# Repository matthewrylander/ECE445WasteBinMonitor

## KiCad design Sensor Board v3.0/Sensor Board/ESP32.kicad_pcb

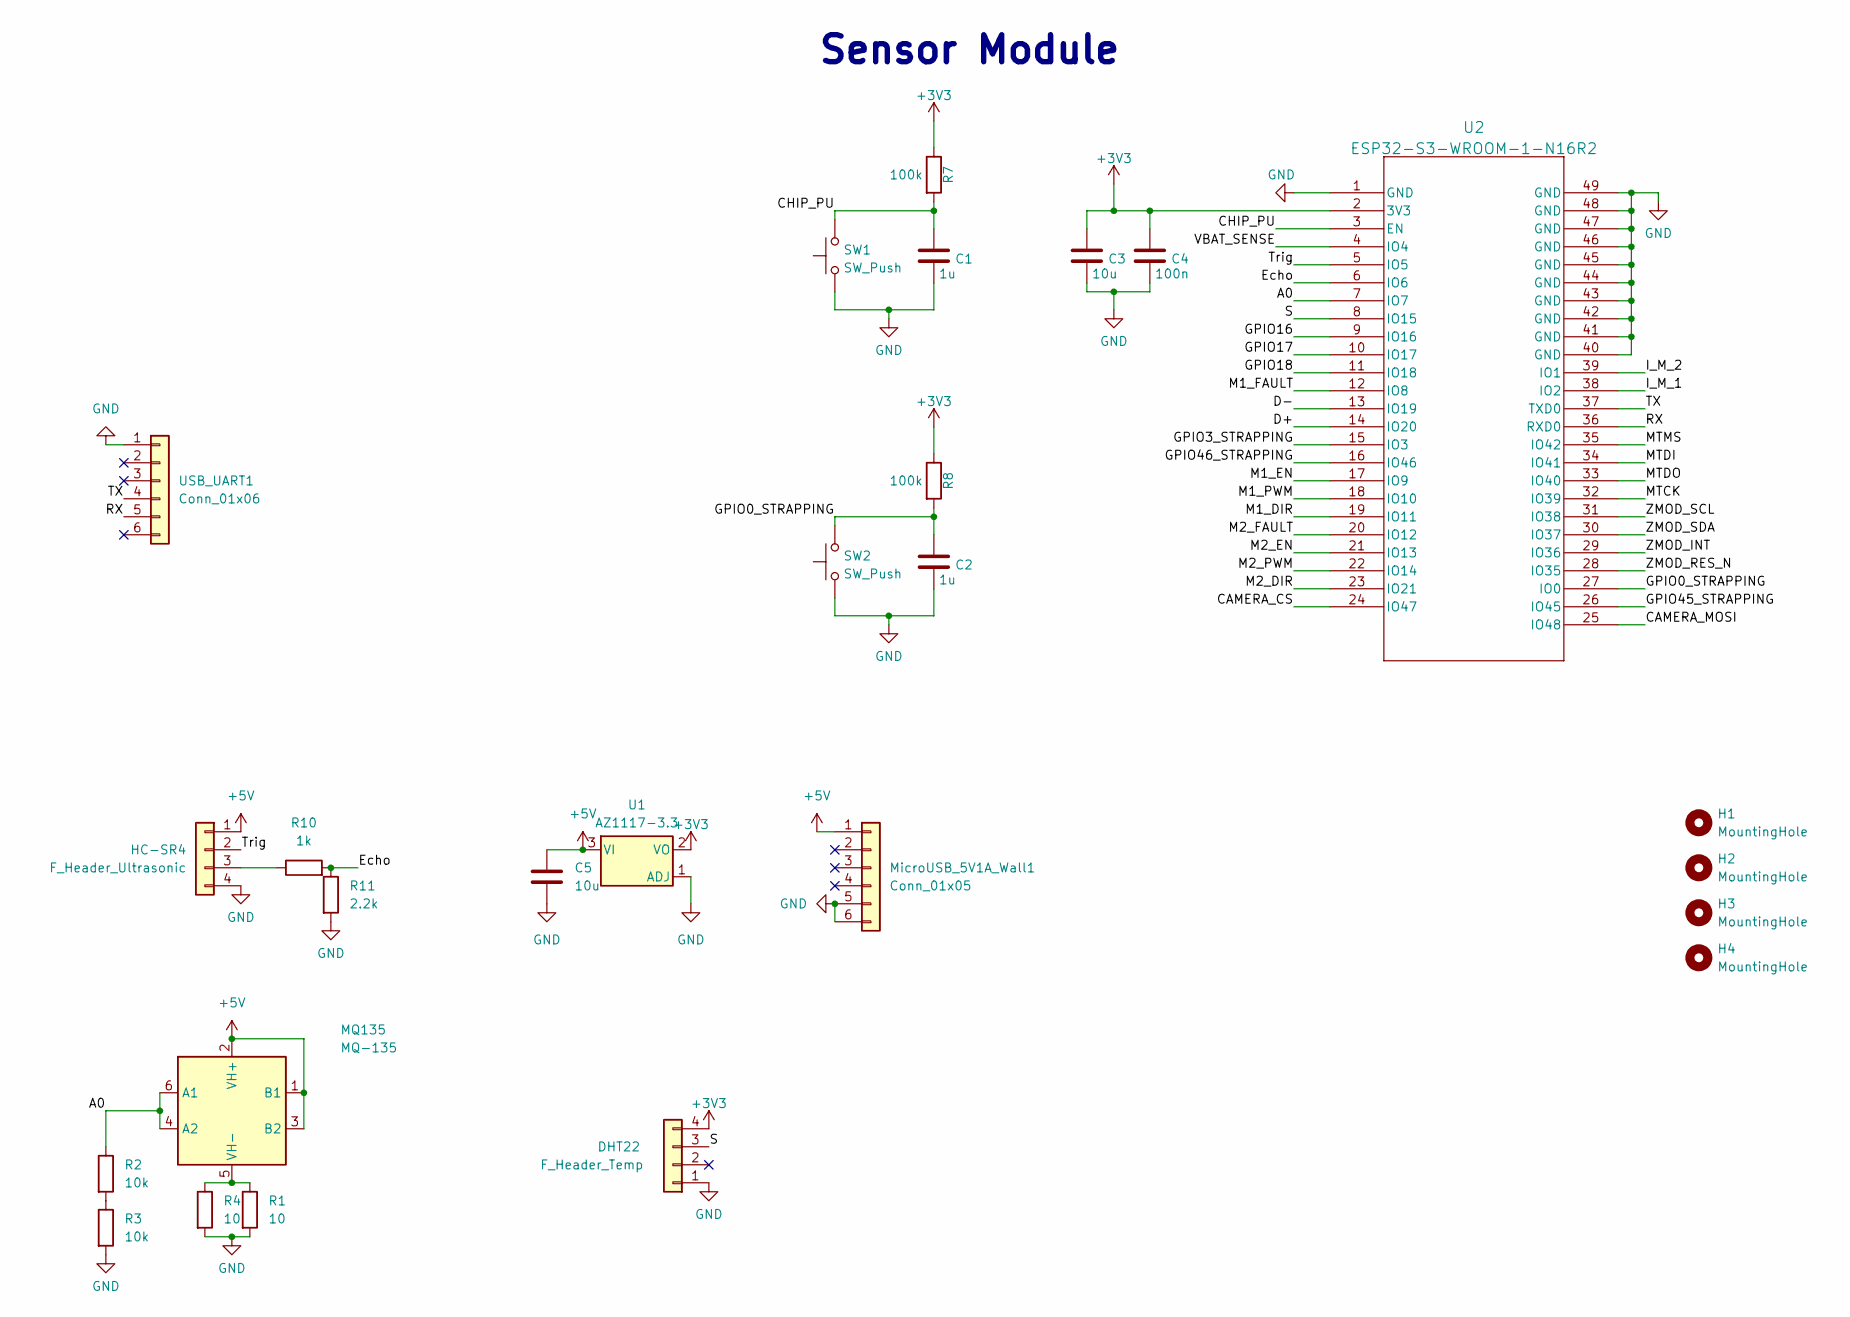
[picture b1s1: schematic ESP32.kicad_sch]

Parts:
C1, C2: 1u; C_0805_2012Metric
C3, C5: 10u; C_0805_2012Metric
C4: 100n; C_0805_2012Metric
DHT22: F_Header_Temp; PinHeader_1x04_P2.54mm_Vertical
H1, H2, H3, H4: MountingHole; MountingHole_3.2mm_M3
HC-SR4: F_Header_Ultrasonic; PinHeader_1x04_P2.54mm_Vertical
MQ135: MQ-135; MQ-6
MicroUSB_5V1A_Wall1: Conn_01x05; USB_Micro-B_Amphenol_10104110_Horizontal
R1, R4: 10; R_Axial_DIN0204_L3.6mm_D1.6mm_P5.08mm_Horizontal
R2, R3: 10k; R_0805_2012Metric
R7, R8: 100k; R_0805_2012Metric
R10: 1k; R_0805_2012Metric
R11: 2.2k; R_0805_2012Metric
SW1, SW2: SW_Push; SW_PUSH_6mm
U1: AZ1117-3.3; AZ1117C-TO252-2
U2: ESP32-S3-WROOM-1-N16R2; ESP32-S3-WROOM-1_EXP
USB_UART1: Conn_01x06; PinHeader_1x06_P2.54mm_Vertical

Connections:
+3V3: C3.1, C4.1, DHT22.4, R7.1, R8.1, U1.2 (VO), U2.2 (3V3)
+5V: C5.1, HC-SR4.1, MQ135.1 (B1), MQ135.2 (VH+), MQ135.3 (B2), MicroUSB_5V1A_Wall1.1, U1.3 (VI)
/A0: MQ135.4 (A2), MQ135.6 (A1), R2.1, U2.7 (IO7)
/CAMERA_CS: U2.24 (IO47)
/CAMERA_MOSI: U2.25 (IO48)
/CHIP_PU: C1.1, R7.2, SW1.2, U2.3 (EN)
/D+: U2.14 (IO20)
/D-: U2.13 (IO19)
/Echo: R10.2, R11.1, U2.6 (IO6)
/GPIO0_STRAPPING: C2.1, R8.2, SW2.2, U2.27 (IO0)
/GPIO3_STRAPPING: U2.15 (IO3)
/GPIO16: U2.9 (IO16)
/GPIO17: U2.10 (IO17)
/GPIO18: U2.11 (IO18)
/GPIO45_STRAPPING: U2.26 (IO45)
/GPIO46_STRAPPING: U2.16 (IO46)
/I_M_1: U2.38 (IO2)
/I_M_2: U2.39 (IO1)
/M1_DIR: U2.19 (IO11)
/M1_EN: U2.17 (IO9)
/M1_FAULT: U2.12 (IO8)
/M1_PWM: U2.18 (IO10)
/M2_DIR: U2.23 (IO21)
/M2_EN: U2.21 (IO13)
/M2_FAULT: U2.20 (IO12)
/M2_PWM: U2.22 (IO14)
/MTCK: U2.32 (IO39)
/MTDI: U2.34 (IO41)
/MTDO: U2.33 (IO40)
/MTMS: U2.35 (IO42)
/RX: U2.36 (RXD0), USB_UART1.5
/S: DHT22.3, U2.8 (IO15)
/TX: U2.37 (TXD0), USB_UART1.4
/Trig: HC-SR4.2, U2.5 (IO5)
/VBAT_SENSE: U2.4 (IO4)
/ZMOD_INT: U2.29 (IO36)
/ZMOD_RES_N: U2.28 (IO35)
/ZMOD_SCL: U2.31 (IO38)
/ZMOD_SDA: U2.30 (IO37)
GND: C1.2, C2.2, C3.2, C4.2, C5.2, DHT22.1, HC-SR4.4, MicroUSB_5V1A_Wall1.5, MicroUSB_5V1A_Wall1.6, R1.2, R3.2, R4.2, R11.2, SW1.1, SW2.1, U1.1 (ADJ), U2.1 (GND), U2.40 (GND), U2.41 (GND), U2.42 (GND), U2.43 (GND), U2.44 (GND), U2.45 (GND), U2.46 (GND), U2.47 (GND), U2.48 (GND), U2.49 (GND), USB_UART1.1
unnamed: HC-SR4.3, R10.1
unnamed: MQ135.5 (VH-), R1.1, R4.1
unnamed: R2.2, R3.1

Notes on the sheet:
Sensor Module

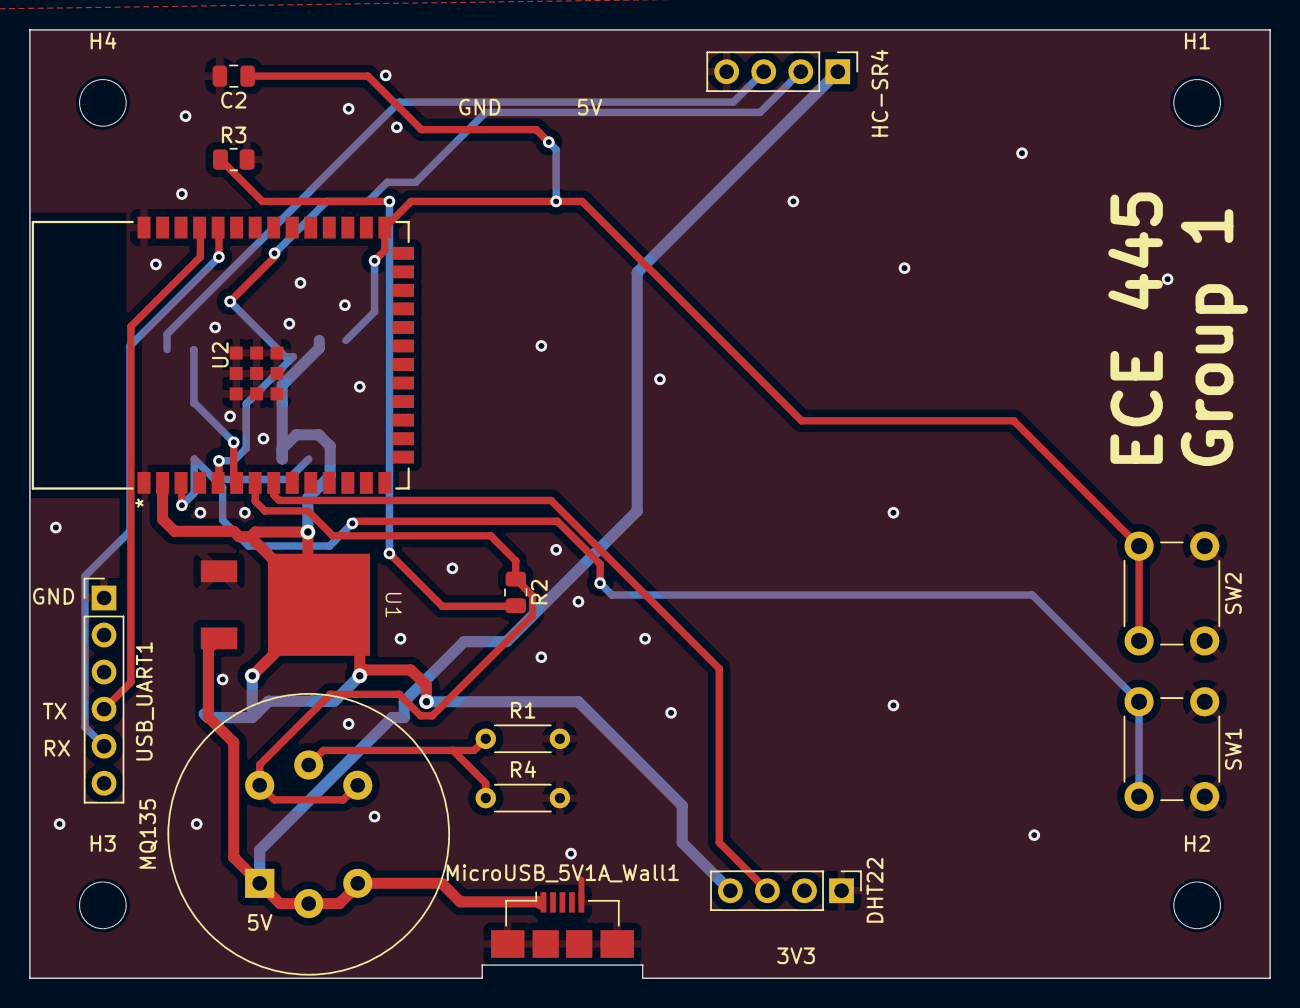
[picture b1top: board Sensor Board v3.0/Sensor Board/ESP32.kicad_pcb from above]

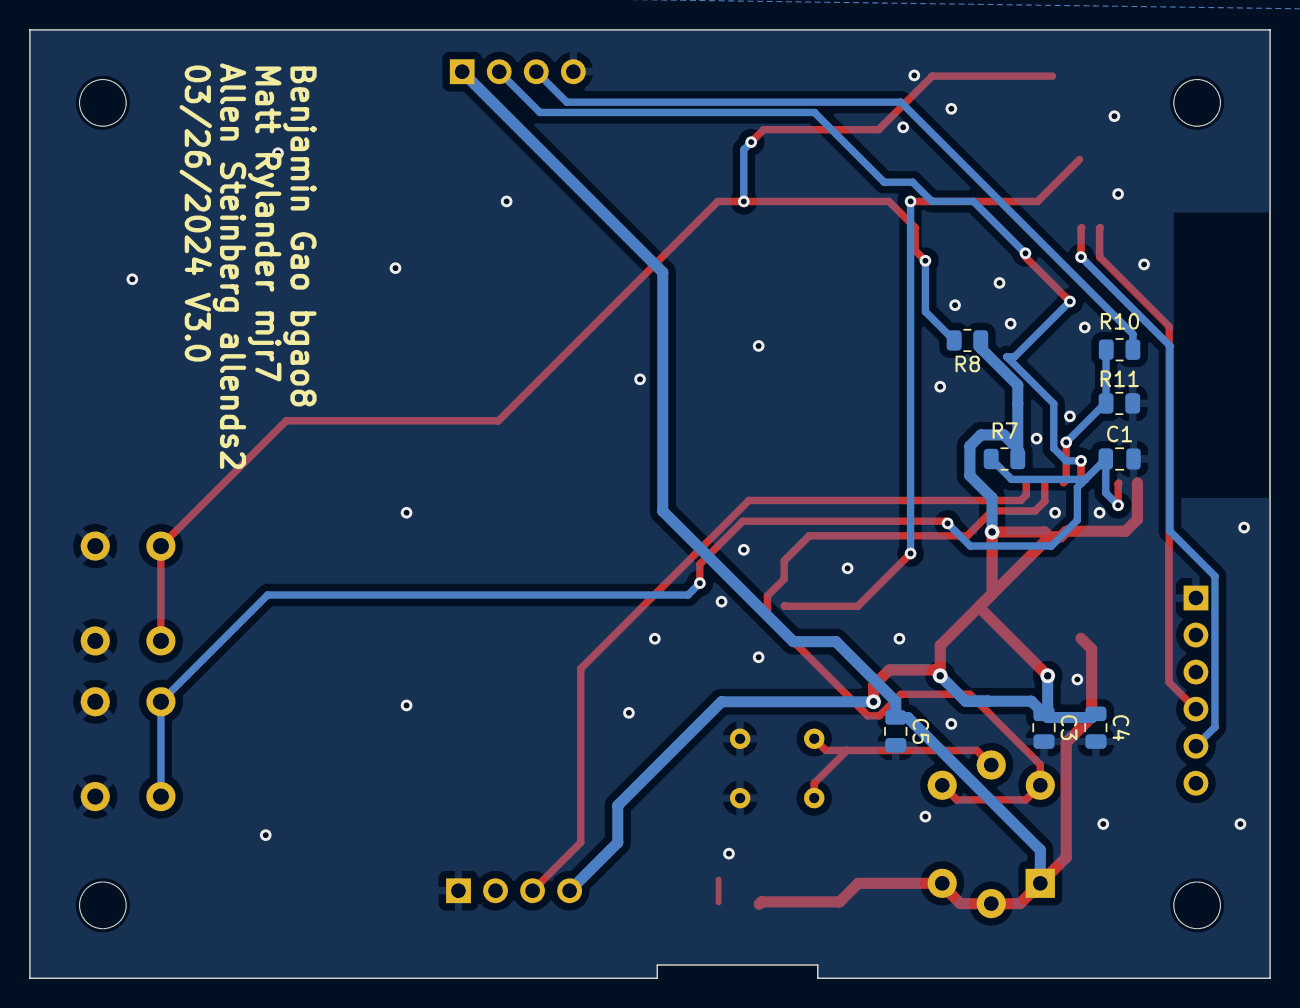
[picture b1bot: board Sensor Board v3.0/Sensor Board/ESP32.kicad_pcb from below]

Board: 2 copper layers, 85.0 x 65.0 mm, 26 parts (8 on the bottom side), 14 nets.

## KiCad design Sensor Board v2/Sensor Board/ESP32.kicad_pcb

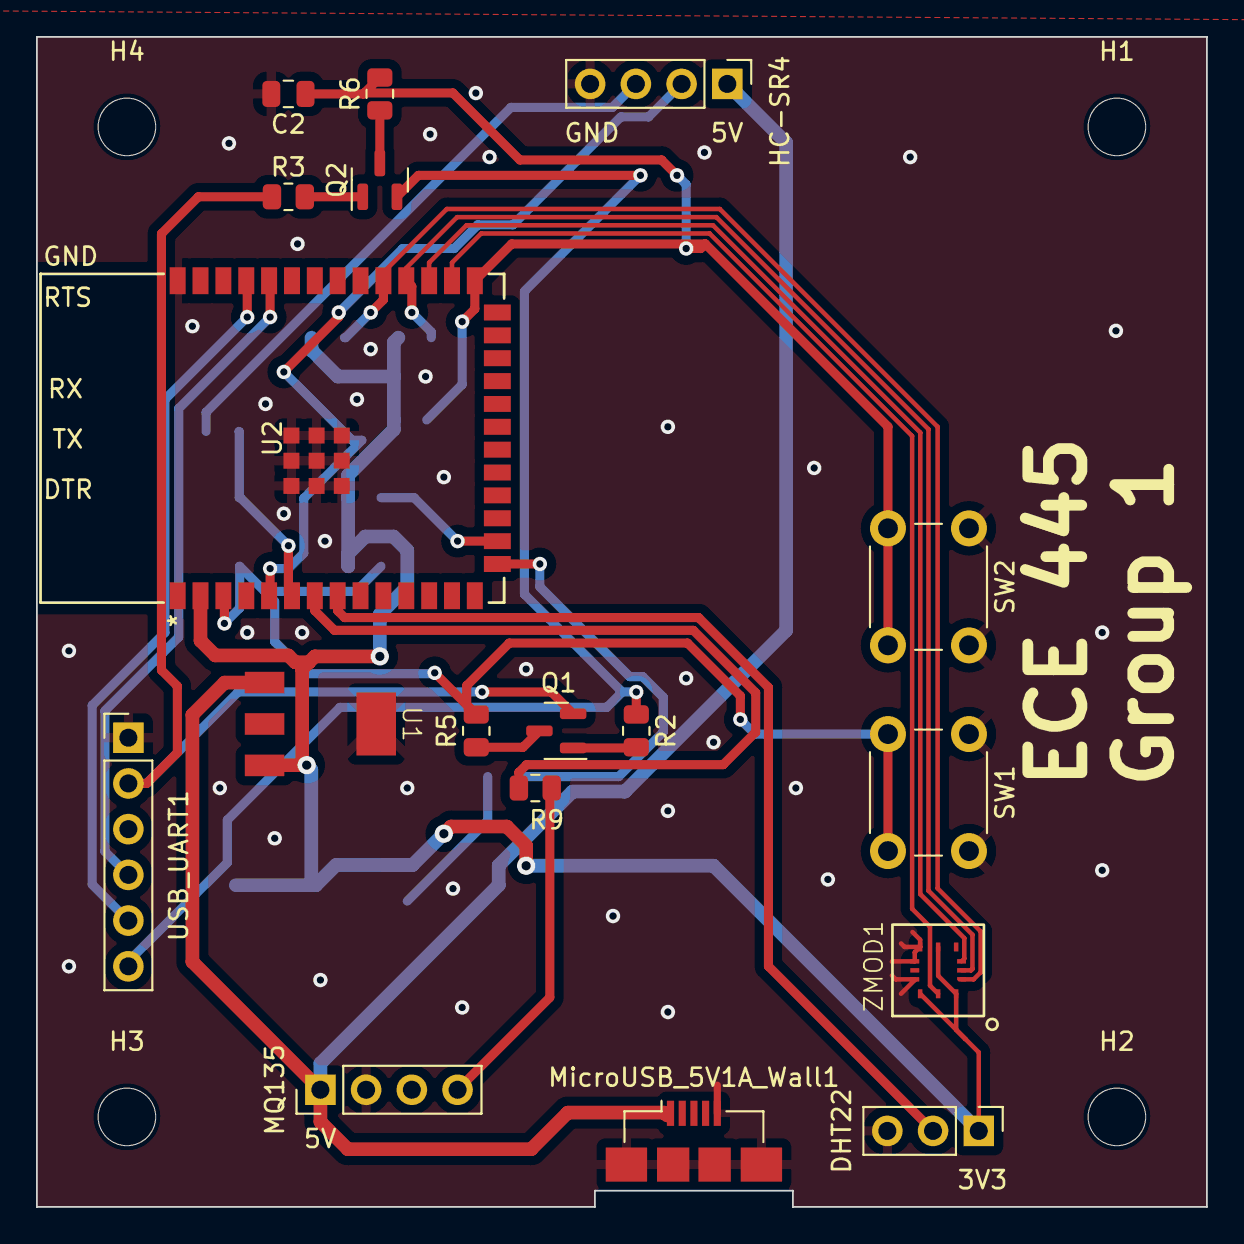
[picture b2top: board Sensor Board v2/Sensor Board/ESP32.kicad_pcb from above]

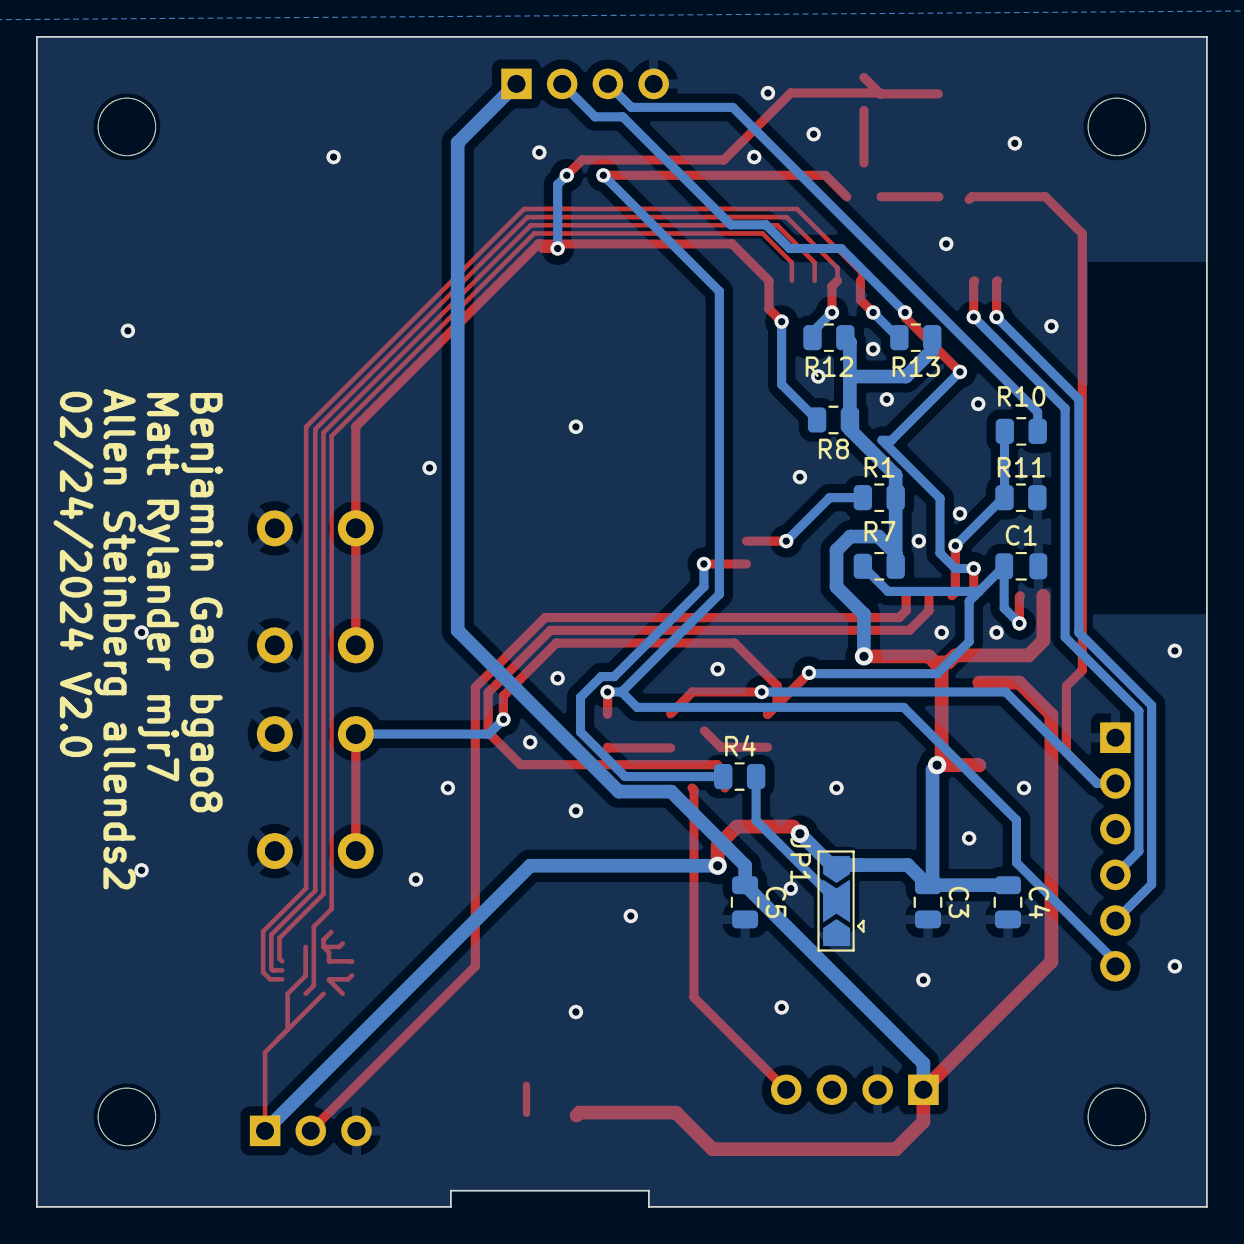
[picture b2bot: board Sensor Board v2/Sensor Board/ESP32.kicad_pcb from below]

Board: 2 copper layers, 65.0 x 65.0 mm, 35 parts (13 on the bottom side), 26 nets.

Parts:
C1, C2: 1u; C_0805_2012Metric
C3, C5: 10u; C_0805_2012Metric
C4: 100n; C_0805_2012Metric
DHT22: F_Header_Temp; PinHeader_1x03_P2.54mm_Vertical
H1, H2, H3, H4: MountingHole; MountingHole_3.2mm_M3
HC-SR4: F_Header_Ultrasonic; PinHeader_1x04_P2.54mm_Vertical
JP1: SolderJumper_3_Open; SolderJumper-3_P2.0mm_Open_TrianglePad1.0x1.5mm
MQ135: Gas Sensor; PinHeader_1x04_P2.54mm_Vertical
MicroUSB_5V1A_Wall1: Conn_01x05; USB_Micro-B_Amphenol_10104110_Horizontal
Q1, Q2: SS8050-G; SOT-23
R1, R4, R9, R10: 1k; R_0805_2012Metric
R2, R3, R5, R6, R12, R13: 10k; R_0805_2012Metric
R7, R8: 100k; R_0805_2012Metric
R11: 2.2k; R_0805_2012Metric
SW1, SW2: SW_Push; SW_PUSH_6mm
U1: AZ1117-3.3; AZ1117C-SOT223
U2: ESP32-S3-WROOM-1-N16R2; ESP32-S3-WROOM-1_EXP
USB_UART1: Conn_01x06; PinHeader_1x06_P2.54mm_Vertical
ZMOD1: ZMOD4410

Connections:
+3V3: C3.1, C4.1, DHT22.1, JP1.3 (B), R1.2, R7.1, R8.1, R12.1, R13.1, U1.3 (VO), U2.2 (3V3), ZMOD1.5 (VDD), ZMOD1.10 (VDDH), ZMOD1.12 (VDDIO)
+5V: C5.1, HC-SR4.1, MQ135.1, MicroUSB_5V1A_Wall1.1, U1.1 (VI)
/A0: R9.1, U2.7 (IO7)
/CHIP_PU: C1.1, R5.2, R7.2, SW1.2, U2.3 (EN)
/DTR: Q2.2 (E), R2.1, USB_UART1.6
/Echo: R10.2, R11.1, U2.6 (IO6)
/GPIO0_STRAPPING: C2.1, R6.2, R8.2, SW2.2, U2.27 (IO0)
/GPIO3_STRAPPING: R4.1, U2.15 (IO3)
/GPIO46_STRAPPING: R1.1, U2.16 (IO46)
/RTS: Q1.2 (E), R3.1, USB_UART1.2
/RX: U2.36 (RXD0), USB_UART1.4
/S: DHT22.2, U2.8 (IO15)
/TX: U2.37 (TXD0), USB_UART1.5
/Trig: HC-SR4.2, U2.5 (IO5)
/ZMOD_INT: U2.29 (IO36), ZMOD1.3 (INT)
/ZMOD_RES_N: U2.28 (IO35), ZMOD1.11 (RES_N)
/ZMOD_SCL: R13.2, U2.31 (IO38), ZMOD1.1 (SCL)
/ZMOD_SDA: R12.2, U2.30 (IO37), ZMOD1.2 (SDA)
GND: C1.2, C2.2, C3.2, C4.2, C5.2, DHT22.3, HC-SR4.4, JP1.1 (A), MQ135.2, MicroUSB_5V1A_Wall1.5, MicroUSB_5V1A_Wall1.6, R11.2, SW1.1, SW2.1, U1.4 (ADJ), U2.1 (GND), U2.40 (GND), U2.41 (GND), U2.42 (GND), U2.43 (GND), U2.44 (GND), U2.45 (GND), U2.46 (GND), U2.47 (GND), U2.48 (GND), U2.49 (GND), USB_UART1.1, ZMOD1.6 (VSS), ZMOD1.7 (VSS), ZMOD1.9 (VSS)
unnamed: HC-SR4.3, R10.1
unnamed: JP1.2 (C), R4.2
unnamed: MQ135.4, R9.2
unnamed: Q1.1 (B), R2.2
unnamed: Q1.3 (C), R5.1
unnamed: Q2.1 (B), R3.2
unnamed: Q2.3 (C), R6.1

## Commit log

2024-01-29 Adding folders for notebooks and photos
2024-02-20 Update Notebook
2024-02-20 Create folder for esp files
2024-02-20 Upload schematic
    Schematic without levelshifter and needing changes
2024-02-20 Update Schematic
2024-02-20 Schematic Updates
2024-02-20 Added voltage regulators to both schematics
2024-02-21 Added PCB for sensor board
    Does not include screw holes. Ignored 4 warnings (silkscreen off board, silkscreen overlap in esp32 which was part of orig footprint, and 2 instances of the solder mask being insufficient on solder b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
2024-02-29 Add hub board v1.0 and Sensor Board v2.0
2024-02-29 Added I2C resistors
2024-03-01 Notebook
2024-03-20 Added Updated Code
2024-03-22 Updated lots of code
2024-03-23 Updated Pinout for initiator
2024-03-26 Uploaded version 2 of sensor board schematic, still needs PCB layout
2024-03-26 Add final sensor board
2024-03-26 Having fun with Nextion display
2024-04-11 updates to code/GUI
2024-04-29 Notebook test
2024-04-29 Notebook pictures
2024-04-29 webp test
2024-05-02 updated code
2024-05-02 updated notebook
2024-05-02 Cleaned up files
